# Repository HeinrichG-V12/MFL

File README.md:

## Interface für das BMW Multifuktionslenkrad
Kompatibel mit allen BMW MFL, die einen 8-bit Bus verwenden und folgende Belegung haben:
- +12v
- IBus
- Tempomatausgang
- Masse

### Die 16-bit Modelle haben dagegen diese Belegung:
- +12v
- Tastenbeleuchtung
- Datenausgang
- Masse

##### Zu erkennen ist die 16-bit Version auch daran, dass das Fahrzeug zusätzlich ein MFL-Modul verbaut hat.

### Verwendete Bauteile:
- MCU: Microchip Atmega2561
- Spannungsregler: Infineon TLE42754
- IBus-Transceiver: Elmos E910.15
- ADC-Beschaltung: hochohmiger Eingang mit Microchip MCP601 Puffer
- Digital Poti: Microchip MCP42050
- RS-232 Interface: TI MAX232

### Es können folgende Radios gesteuert werden:
- Pioneer/Sony/JVC mit eine RW Eingang
- Becker mit einem RS232 Eingang

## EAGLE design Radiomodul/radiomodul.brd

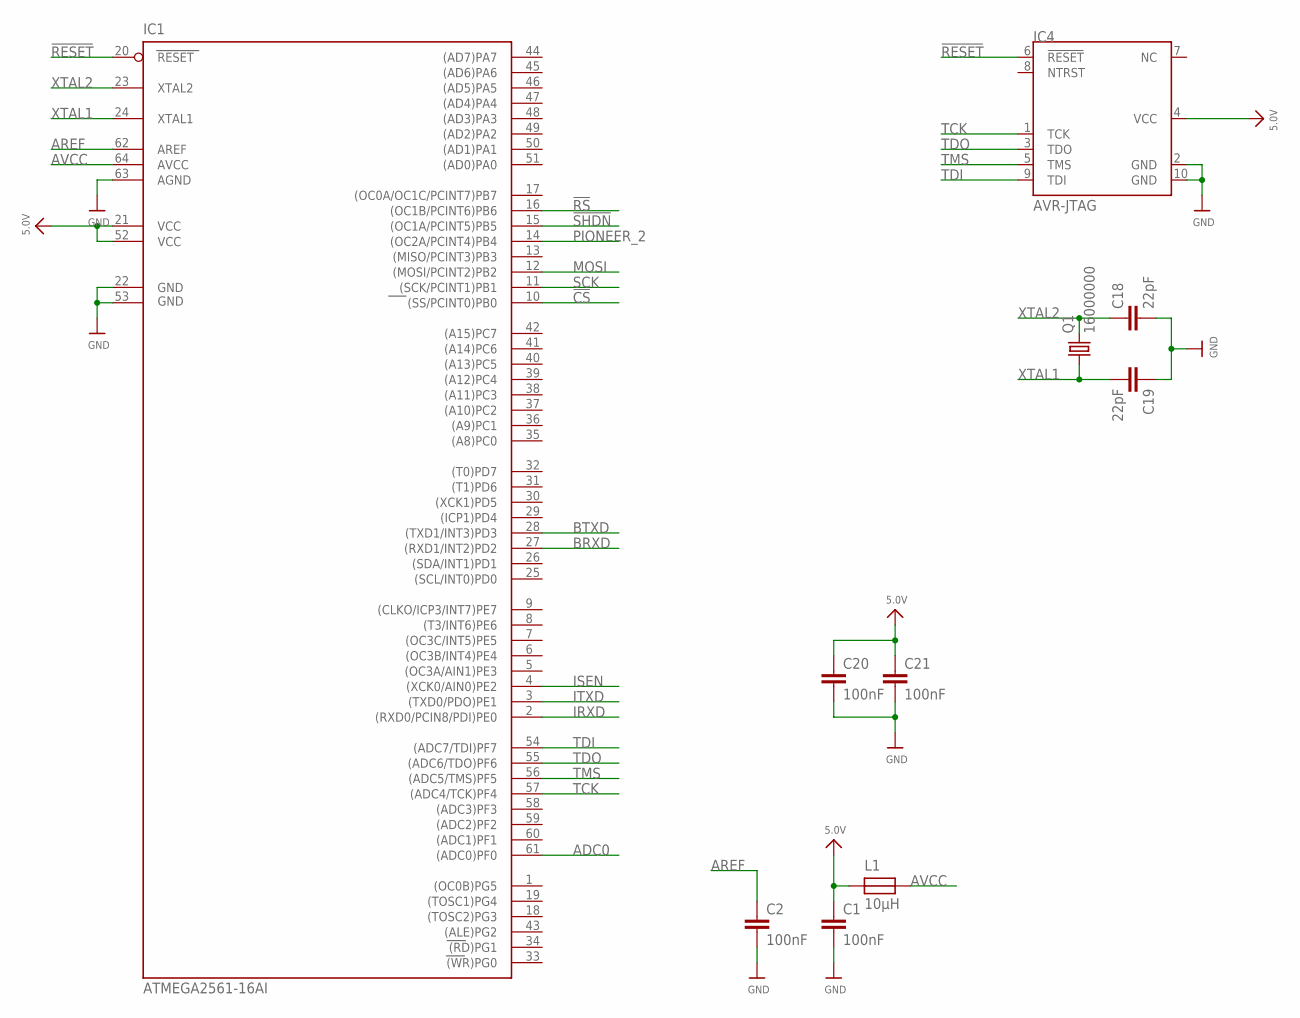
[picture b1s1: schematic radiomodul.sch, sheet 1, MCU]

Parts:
C1, C2, C20, C21: 100nF; C0805
C18, C19: 22pF; C0805
IC1: ATMEGA2561-16AI; TQFP64
IC4: AVR-JTAG; 2X05_1.27MM_SMT
L1: 10µH; 1206
Q1: 16000000; HC49UP

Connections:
5.0V: C1.1, C20.1, C21.1, IC1.21 (VCC), IC1.52 (VCC1), IC4.4 (VCC), L1.1; also elsewhere on the board
!CS: IC1.10 ((SS/PCINT0)PB0); also elsewhere on the board
!RESET: IC1.20 (RESET), IC4.6 (!RESET); also elsewhere on the board
!RS: IC1.16 ((OC1B/PCINT6)PB6); also elsewhere on the board
!SHDN: IC1.15 ((OC1A/PCINT5)PB5); also elsewhere on the board
ADC0: IC1.61 ((ADC0)PF0); also elsewhere on the board
AREF: C2.1, IC1.62 (AREF)
AVCC: IC1.64 (AVCC), L1.2
BRXD: IC1.27 ((RXD1/INT2)PD2); also elsewhere on the board
BTXD: IC1.28 ((TXD1/INT3)PD3); also elsewhere on the board
GND: C1.2, C2.2, C18.2, C19.1, C20.2, C21.2, IC1.22 (GND), IC1.53 (GND1), IC1.63 (AGND), IC4.2 (GND), IC4.10 (GND); also elsewhere on the board
IRXD: IC1.2 ((RXD0/PCIN8/PDI)PE0); also elsewhere on the board
ISEN: IC1.4 ((XCK0/AIN0)PE2); also elsewhere on the board
ITXD: IC1.3 ((TXD0/PDO)PE1); also elsewhere on the board
MOSI: IC1.12 ((MOSI/PCINT2)PB2); also elsewhere on the board
PIONEER_2: IC1.14 ((OC2A/PCINT4)PB4); also elsewhere on the board
SCK: IC1.11 ((SCK/PCINT1)PB1); also elsewhere on the board
TCK: IC1.57 ((ADC4/TCK)PF4), IC4.1 (TCK)
TDI: IC1.54 ((ADC7/TDI)PF7), IC4.9 (TDI)
TDO: IC1.55 ((ADC6/TDO)PF6), IC4.3 (TDO)
TMS: IC1.56 ((ADC5/TMS)PF5), IC4.5 (TMS)
XTAL1: C19.2, IC1.24 (XTAL1), Q1.1
XTAL2: C18.1, IC1.23 (XTAL2), Q1.2

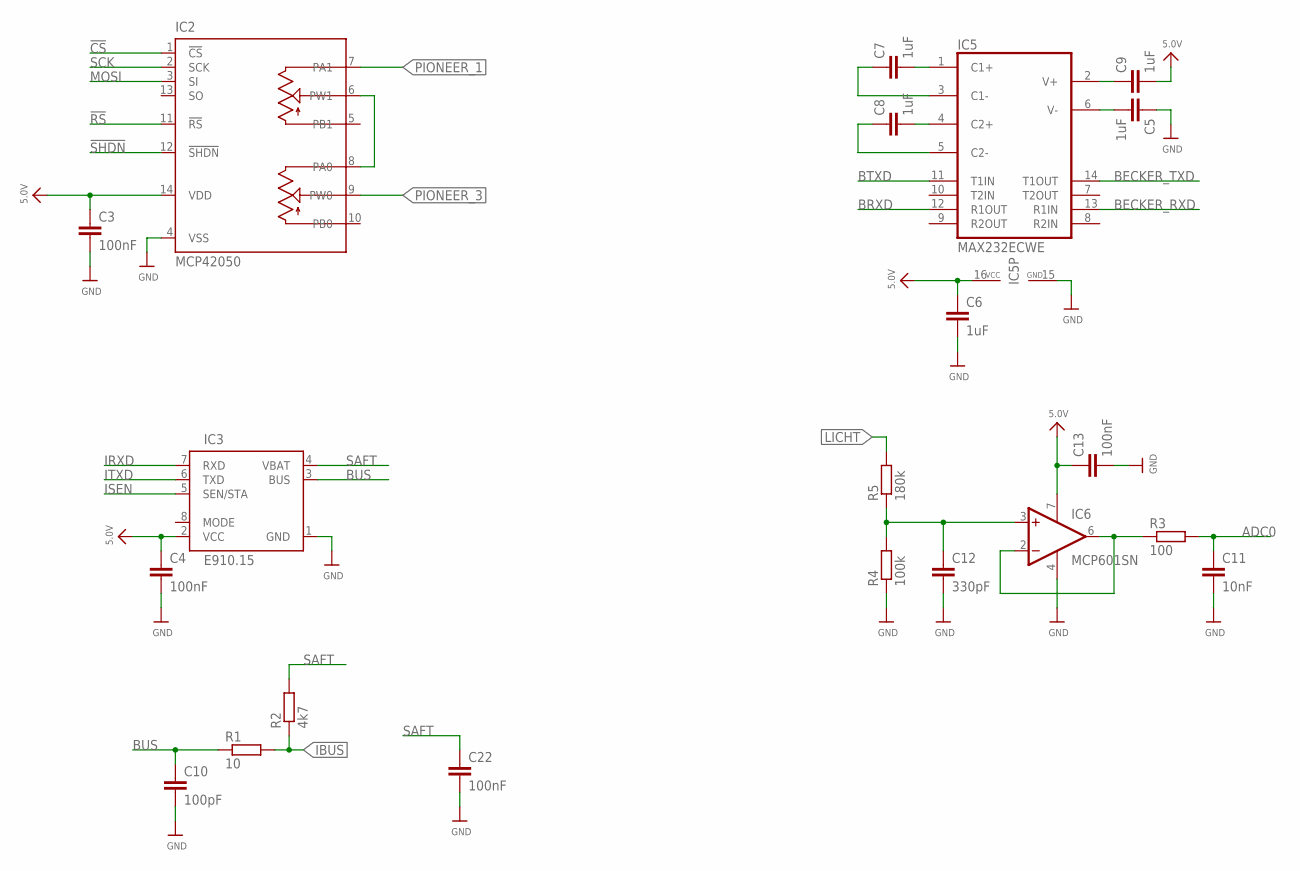
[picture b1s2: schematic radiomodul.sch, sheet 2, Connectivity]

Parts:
C3, C4, C13, C22: 100nF; C0805
C5, C6, C7, C8, C9: 1uF; C0805
C10: 100pF; C0805
C11: 10nF; C0805
C12: 330pF; C0805
IC2: MCP42050; SO-14
IC3: E910.15; SO8
IC5: MAX232ECWE; SO16L
IC6: MCP601SN; SO08
R1: 10; R0805
R2: 4k7; R0805
R3: 100; R0805
R4: 100k; R0805
R5: 180k; R0805

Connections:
5.0V: C3.1, C4.1, C6.1, C9.2, C13.1, IC2.14 (VDD), IC3.2 (VCC), IC5.16 (VCC), IC6.7 (V+); also elsewhere on the board
!CS: IC2.1 (!CS); also elsewhere on the board
!RS: IC2.11 (!RS); also elsewhere on the board
!SHDN: IC2.12 (!SHDN); also elsewhere on the board
ADC0: C11.1, R3.2; also elsewhere on the board
BECKER_RXD: IC5.13 (R1IN); also elsewhere on the board
BECKER_TXD: IC5.14 (T1OUT); also elsewhere on the board
BRXD: IC5.12 (R1OUT); also elsewhere on the board
BTXD: IC5.11 (T1IN); also elsewhere on the board
BUS: C10.1, IC3.3 (BUS), R1.1
GND: C3.2, C4.2, C5.1, C6.2, C10.2, C11.2, C12.2, C13.2, C22.2, IC2.4 (VSS), IC3.1 (GND), IC5.15 (GND), IC6.4 (V-), R4.1; also elsewhere on the board
IBUS: R1.2, R2.1; also elsewhere on the board
IRXD: IC3.7 (RXD); also elsewhere on the board
ISEN: IC3.5 (SEN/STA); also elsewhere on the board
ITXD: IC3.6 (TXD); also elsewhere on the board
LICHT: R5.2; also elsewhere on the board
MOSI: IC2.3 (SI); also elsewhere on the board
unnamed: C5.2, IC5.6 (V-)
unnamed: C7.1, IC5.3 (C1-)
unnamed: C12.1, IC6.3 (+IN), R4.2, R5.1
unnamed: C8.1, IC5.5 (C2-)
unnamed: IC6.2 (-IN), IC6.6 (OUT), R3.1
unnamed: C8.2, IC5.4 (C2+)
unnamed: IC2.6 (PW1), IC2.8 (PA0)
unnamed: C9.1, IC5.2 (V+)
unnamed: C7.2, IC5.1 (C1+)
PIONEER_1: IC2.7 (PA1); also elsewhere on the board
PIONEER_3: IC2.9 (PW0); also elsewhere on the board
SAFT: C22.1, IC3.4 (VBAT), R2.2; also elsewhere on the board
SCK: IC2.2 (SCK); also elsewhere on the board

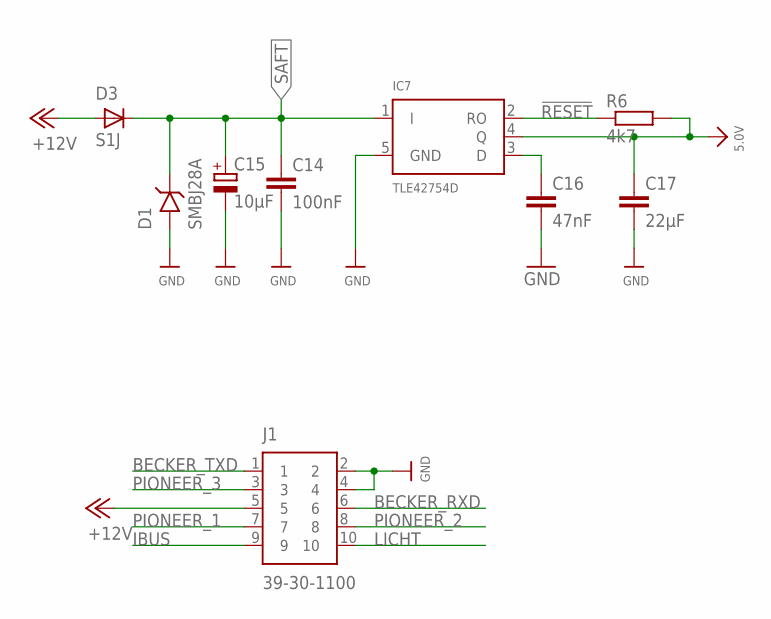
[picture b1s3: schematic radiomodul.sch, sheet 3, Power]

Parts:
C14: 100nF; C0805
C15: 10µF; PANASONIC_D
C16: 47nF; C0805
C17: 22µF; C1206
D1: SMBJ28A; DO-214AA
D3: S1J; SMADIODE
IC7: TLE42754D; TO252-51
J1: 39-30-1100
R6: 4k7; R0805

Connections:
5.0V: C17.1, IC7.4 (Q), R6.2; also elsewhere on the board
!RESET: IC7.2 (RO), R6.1; also elsewhere on the board
+12V: D3.A, J1.5
BECKER_RXD: J1.6; also elsewhere on the board
BECKER_TXD: J1.1; also elsewhere on the board
GND: C14.2, C15.-, C16.2, C17.2, D1.P$2 (A), IC7.5 (GND), J1.2, J1.4; also elsewhere on the board
IBUS: J1.9; also elsewhere on the board
LICHT: J1.10; also elsewhere on the board
unnamed: C16.1, IC7.3 (D)
PIONEER_1: J1.7; also elsewhere on the board
PIONEER_2: J1.8; also elsewhere on the board
PIONEER_3: J1.3; also elsewhere on the board
SAFT: C14.1, C15.+, D1.P$1 (C), D3.C, IC7.1 (I); also elsewhere on the board

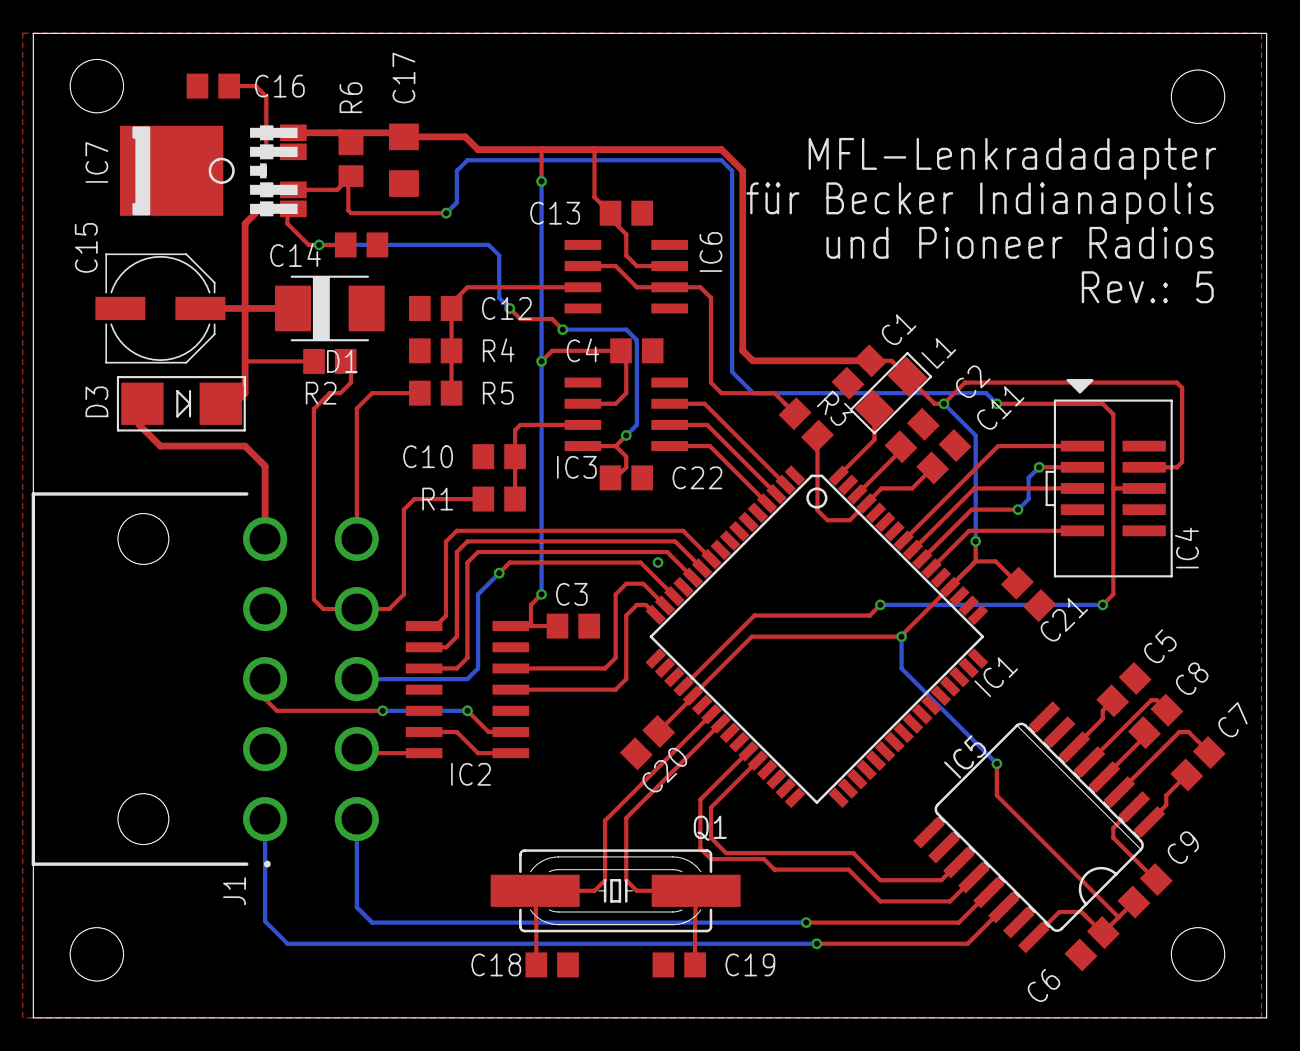
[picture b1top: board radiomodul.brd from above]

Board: 2 copper layers, 74.0 x 59.0 mm, 40 parts (0 on the bottom side), 42 nets.

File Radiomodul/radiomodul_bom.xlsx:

Qty | Value | Device | Package | Parts | Description
1 | 10 | R-EU_R0805 | R0805 | R1 | RESISTOR, European symbol
1 | 100 | R-EU_R0805 | R0805 | R3 | RESISTOR, European symbol
1 | 100k | R-EU_R0805 | R0805 | R4 | RESISTOR, European symbol
13 | 100nF | C-EUC0805 | C0805 | C1, C2, C3, C4, C6, C7, C8, C9, C13, C14, C20, C21, C22 | CAPACITOR, European symbol
1 | 100pF | C-EUC0805 | C0805 | C10 | CAPACITOR, European symbol
1 | 10nF | C-EUC0805 | C0805 | C11 | CAPACITOR, European symbol
1 | 10µF | CPOL-EUD | PANASONIC_D | C15 | POLARIZED CAPACITOR, European symbol
1 | 10µH | FERRITE1206 | 1206 | L1 | Ferrite Bead
1 | 16000000 | CRYSTALHC49UP | HC49UP | Q1 | CRYSTAL
1 | 180k | R-EU_R0805 | R0805 | R5 | RESISTOR, European symbol
2 | 18pF | C-EUC0805 | C0805 | C18, C19 | CAPACITOR, European symbol
1 | 22µF | C-EUC1206 | C1206 | C17 | CAPACITOR, European symbol
1 | 330pF | C-EUC0805 | C0805 | C12 | CAPACITOR, European symbol
1 | 39-30-1100 | 39-30-1100 | 39-30-1100 | J1 | 10 way r/a PCB header w/peg,Mini-Fit Jr Molex MINI-FIT JR. Series, Series Numbe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
1 | 47nF | C-EUC0805 | C0805 | C16 | CAPACITOR, European symbol
2 | 4k7 | R-EU_R0805 | R0805 | R2, R6 | RESISTOR, European symbol
1 | ATMEGA2561-16AI | ATMEGA2561-16AI | TQFP64 | IC1 | MICROCONTROLLER
1 | AVR-JTAG | AVR-JTAG | 2X05_1.27MM_SMT | IC4
1 | E910.15 | E910.15 | SO8 | IC3 | Elmos E910.15
1 | MAX232ECWE | MAX232ECWE | SO16L | IC5 | RS232 TRANSCEIVER
1 | MCP42050 | MCP42050 | SO-14 | IC2 | The MCP42050 digital potentiometer features two independent channels,
1 | MCP601SN | MCP601SN | SO08 | IC6 | Single Op Amp 2.7V to 6.0V Single Supply CMOS
1 | S1J | DIODESMA | SMADIODE | D3 | Diode
1 | SMBJ28A | P6SMBXXASMB | DO-214AA | D1 | SMBxxAT3G TVS Diode
1 | TLE42754D | TLE42754D | TO252-51 | IC7

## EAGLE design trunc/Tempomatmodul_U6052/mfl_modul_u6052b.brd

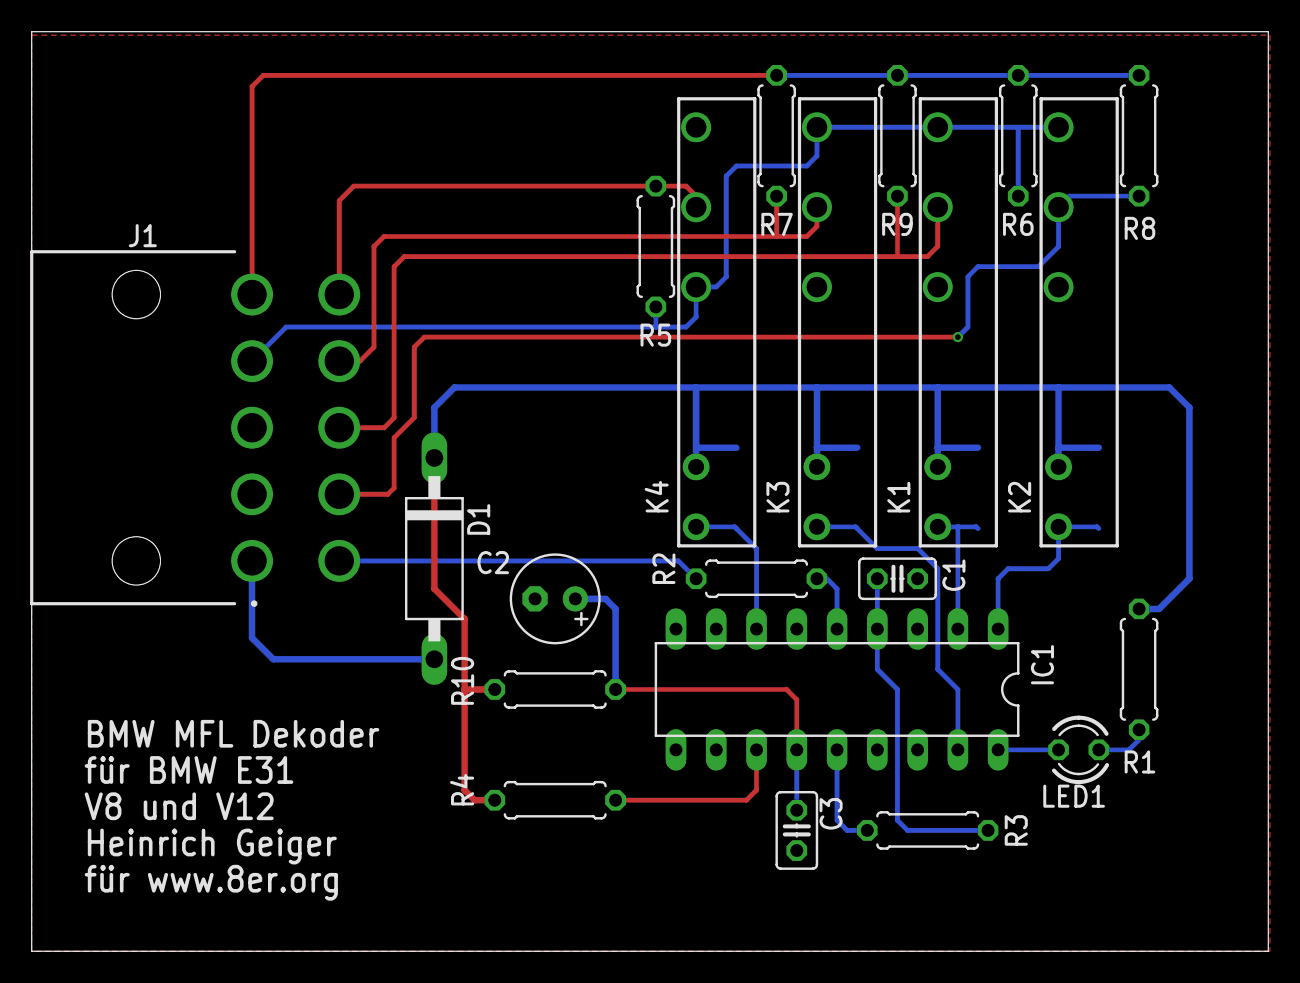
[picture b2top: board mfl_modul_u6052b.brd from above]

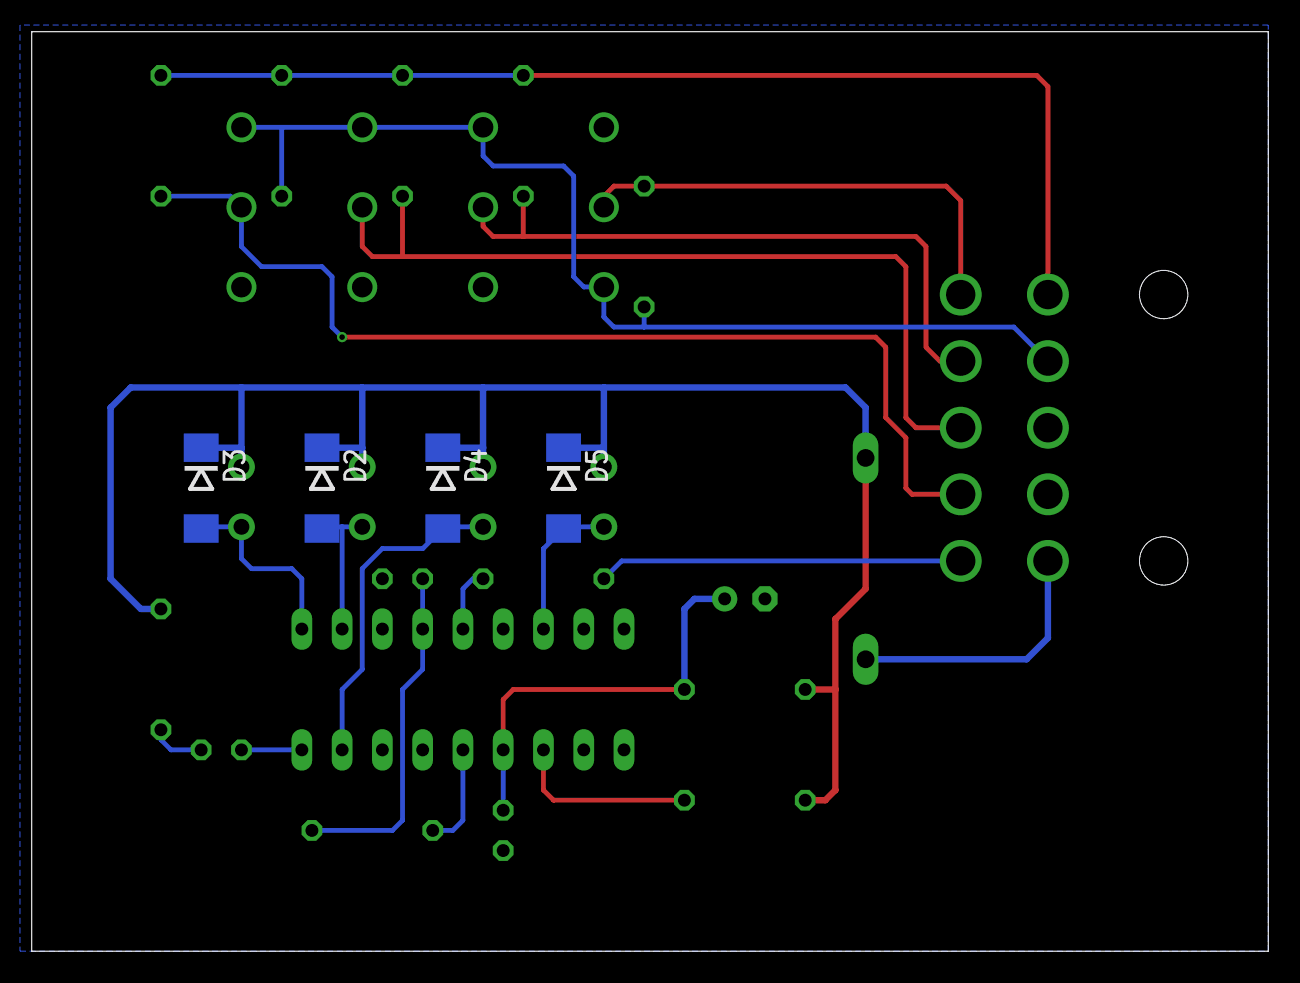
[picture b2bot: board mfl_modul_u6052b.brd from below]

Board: 2 copper layers, 78.0 x 58.0 mm, 25 parts (4 on the bottom side), 21 nets.

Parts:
C1: 680pF; C025-025X050
C2: 100uF/36V; E2,5-6
C3: 100nF; C025-025X050
D1: EP20D; DO15-12
D2, D3, D4, D5: MBSR140; DO214AA
IC1: U6052B-A; DIL18
J1: 39-30-1100
K1, K2, K3, K4: APF30212C
LED1: led grün 2,2v 20mA; LED3MM
R1: 560; 0207/7
R2: 100; 0207/7
R3: 69k8; 0207/7
R4, R8: 200; 0207/7
R5: 931; 0207/7
R6, R7: 665; 0207/7
R9: 66,5; 0207/7
R10: 510; 0207/7

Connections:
ABRUF: D3.A, IC1.1, K2.1
EML1: J1.5, R6.2, R7.2, R8.2, R9.2
EML2/X72.4: J1.10, K4.COM, R5.1
GND: C1.2, C2.-, C3.2, IC1.3, IC1.9, IC1.15, J1.2
I/O: D5.A, IC1.7, K4.1
MFL: J1.6, R2.1
MINUS: D4.A, IC1.17, K3.1
unnamed: IC1.5, R2.2
unnamed: IC1.12, R4.2
unnamed: LED1.A, R1.1
unnamed: IC1.18, LED1.K
OSC: C1.1, IC1.4, R3.2
PLUS: D2.A, IC1.2, K1.1
VBAT: D1.A, J1.1
VCC: D1.C, D2.C, D3.C, D4.C, D5.C, K1.2, K2.2, K3.2, K4.2, R1.2, R4.1, R10.1
VS: C2.+, C3.1, IC1.13, R10.2
VSTAB: IC1.14, R3.1
X72.1: J1.4, K1.NO, K2.NO, K3.NO, K4.NC, R5.2, R6.1
X72.2: J1.7, K2.COM, R8.1
X72.3: J1.9, K3.COM, R7.1
X72.7: J1.8, K1.COM, R9.1

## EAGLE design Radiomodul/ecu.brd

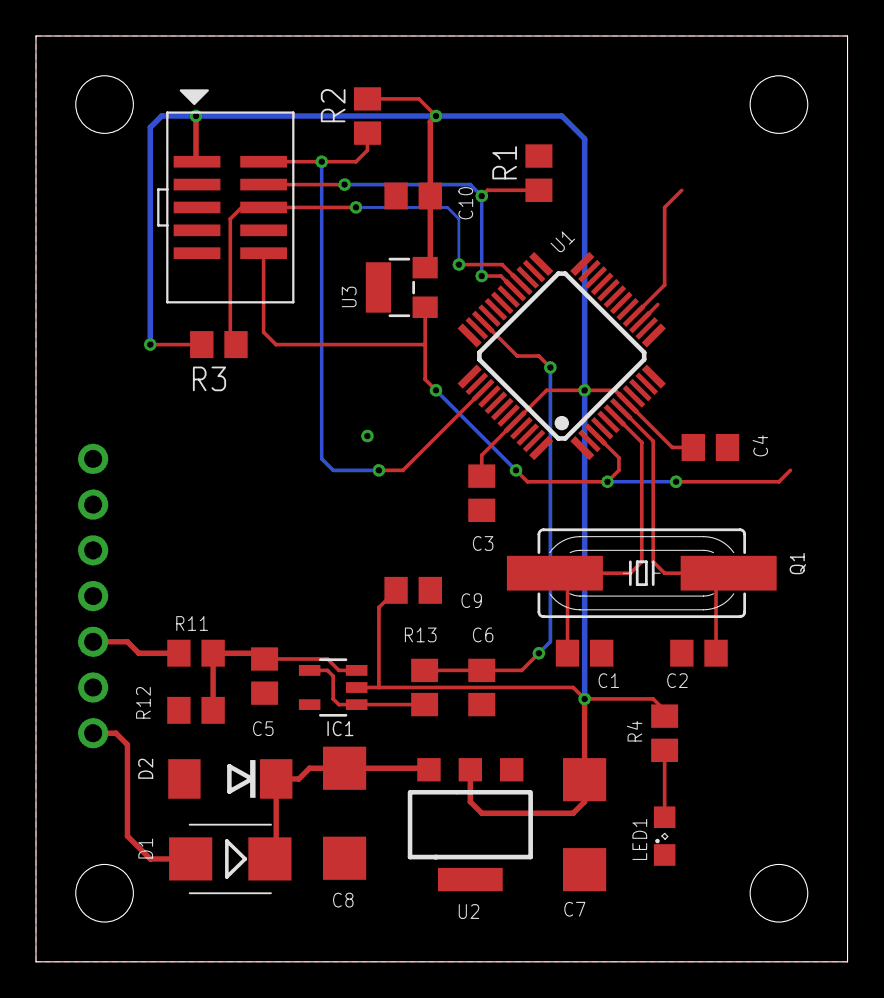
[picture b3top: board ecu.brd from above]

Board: 2 copper layers, 45.1 x 51.4 mm, 27 parts (0 on the bottom side), 15 nets.

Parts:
C1, C2: 22pF; C0805
C3, C4, C9, C10: 100nF; C0805
C5: 330pF; C0805
C6: 10nF; C0805
C7, C8: 10uF; SMC_C
D1: SMB
D2: P6SMB18CA; DO214AA
IC1: MCP601R; SOT23-5
JP2: E31; 1X07_ROUND
JTAG1: SWD; 2X05_1.27MM_SMT
LED1: Power; SML0805
Q1: 12MHz; HC49UP
R1, R2, R3: 10k; R0805
R4: 56; R0805
R11: 620k; R0805
R12: 100k; R0805
R13: 100; R0805
U1: LPC1343FBD48; SOT313-2
U2: LM1117-3.3; SOT223-R
U3: MCP130T; SOT23-W

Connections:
3.3V: C3.1, C4.1, C7.+, C9.1, C10.1, IC1.2, JTAG1.1, R2.2, R3.2, R4.2, U1.8, U1.44, U2.2, U3.2
12V: D1.A, JP2.1
/RESET: JTAG1.10, U1.3, U3.1
ADC: C6.1, R13.2, U1.34
GND: C1.2, C2.1, C3.2, C4.2, C5.2, C6.2, C7.-, C8.-, C9.2, C10.2, D2.A, IC1.5, JP2.2, JTAG1.3, JTAG1.5, JTAG1.9, LED1.C, R1.2, R12.1, U1.5, U1.41, U2.1, U3.3
LICHT: JP2.3, R11.2
unnamed: C8.+, D1.C, D2.C, U2.3
unnamed: IC1.1, IC1.4, R13.1
unnamed: LED1.A, R4.1
unnamed: C5.1, IC1.3, R11.1, R12.2
SWCLK: JTAG1.4, R1.1, U1.29
SWDIO: JTAG1.2, R2.1, U1.39
SWO: JTAG1.6, R3.1, U1.28
XTALIN: C1.1, Q1.2, U1.6
XTALOUT: C2.2, Q1.1, U1.7

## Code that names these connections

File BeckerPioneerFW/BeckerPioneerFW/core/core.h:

/*
 * core.h
 *
 * Created: 20.06.2021 20:08:32
 *  Author: Heinrich
 */ 

#include <avr/io.h>

#ifndef CORE_H_
#define CORE_H_

// digipot ports and pins
#define MCP_HW_INT			DDRB
#define MCP_HW_INT_PORT		PORTB
#define RING				PB4
#define MCP_SHDN			PB5
#define MCP_RST				PB6

// spi ports and pins
#define DDR_CS				DDRB
#define DDR_SPI				DDRB
#define DD_CS				PB0
#define DD_SCK				PB1
#define DD_MOSI				PB2

void ports_pins_init (void);



#endif /* CORE_H_ */

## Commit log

2019-05-01 initial import
2019-10-14 Fixed. Running version!
2019-10-14 first running version.
2019-10-28 Fosc corrected
2019-10-30 Initial import.
2019-11-01 add adc lib add set_brigh function for setting brightness of mfl illumination
2019-11-02 added ad5243 added ibus_network some corrections and refactorings
2019-11-07 timer added some refactorings in uart
2019-11-13 the name corrected
2019-11-17 RX and TX buffer added
2020-01-03 Support only for V12 engines (M70 and M73)
2020-01-03 Added support for V8 engines (M60 and M62)
2020-01-26 refactoring
2020-03-21 MFL Radio interface done.
2020-04-03 buffer added
2020-04-03 mfl brightness function renamed
2020-04-04 some changes in SPI
2020-04-05 changed F_CPU to 16000000Hz
    adapted timer to new F_CPU
    adapted UARTs to new F_CPU
    start implementation of ibus processor
    created radio_controller interface
    calculated values for pioneer radio
2020-04-06 some parts changed, BOM added
2020-04-06 interrupt to receive ibus messages implemented
2020-04-24 working version!
2020-04-24 adc_activated
    set_brightness corrected
    some clean ups
2020-04-25 added asynchronous initialization of becker and pioneer interfaces
    added asynchronous sending of releaser command on becker interface
    *NOT TESTED YET!*
2020-04-27 UART1 fixed
    asynchronous communication with radios improved
    release corrected
    ibus_processor corrected
    some refactorings
2020-04-27 AD5293 added
2020-04-28 pioneer 2 added
    AD5293 added
    MCP42050 removed
2020-04-30 adc offset added
    300ms scheduler timer implemented
    sen/sta pin handling corrected / ibus sending routine
2020-05-01 Initialization of scheduler implemented
2020-05-15 eagle stuff added
2020-05-15 some small modifications.
2020-05-25 a lot of changes....
    tested functions of MFL:
    -> volume increase and decrease
    -> next and previous track
2020-06-07 some AD5293 functions implemented
    some small bugfixes
2020-06-10 Released version!
2020-12-30 Migrated to new Atmel Studio version
2021-01-23 -> removed ad5293 libraries -> added handling for hardware reset and shutdown -> some small refactorings
2021-02-02 some files deleted
2021-02-04 board and schematic replaced
2021-02-04 project description added
2021-06-21 implemented hw control of mcp42xxx added core pin init
2021-06-21 lPC13xx implementation dropped
2021-06-22 TIMER4 fixed, some clean ups
2021-09-04 Radiomodul_fw deleted
2021-09-04 first commit after removing Becker stuff

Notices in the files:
parts and their libraries:
microbuilder: This work is placed in the public domain, and may be freely used for commercial and non-commercial work with the following conditions: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
